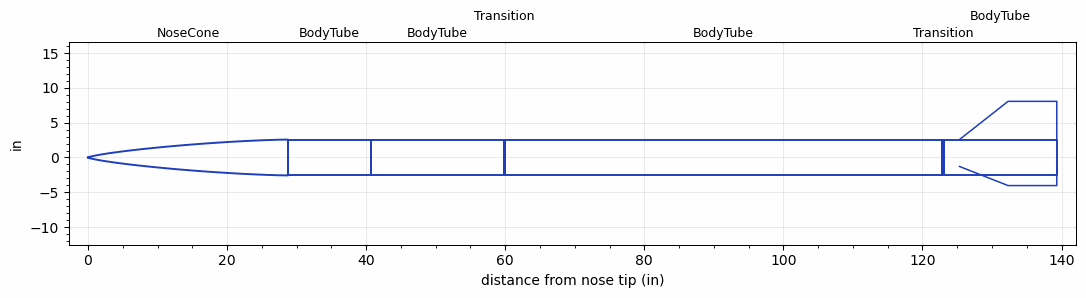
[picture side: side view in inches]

<RASAeroDocument>
 <FileVersion>2</FileVersion>
 <RocketDesign>
  <NoseCone>
   <Length>28.75</Length>
   <Diameter>5.15</Diameter>
   <Shape>Von Karman Ogive</Shape>
   <BluntRadius>0.125</BluntRadius>
   <Location>0</Location>
  </NoseCone>
  <BodyTube>
   <Length>12</Length>
   <Diameter>5.15</Diameter>
   <Location>28.75</Location>
  </BodyTube>
  <BodyTube>
   <Length>19</Length>
   <Diameter>5.15</Diameter>
   <LaunchShoeArea>0.1</LaunchShoeArea>
   <Location>40.75</Location>
  </BodyTube>
  <Transition>
   <Length>0.25</Length>
   <Diameter>5</Diameter>
   <Location>59.75</Location>
   <RearDiameter>5</RearDiameter>
  </Transition>
  <BodyTube>
   <Length>62.812</Length>
   <Diameter>5</Diameter>
   <Location>60</Location>
  </BodyTube>
  <Transition>
   <Length>0.25</Length>
   <Diameter>5.15</Diameter>
   <Location>122.812</Location>
   <RearDiameter>5.15</RearDiameter>
  </Transition>
  <BodyTube>
   <Length>16.25</Length>
   <Diameter>5.15</Diameter>
   <LaunchShoeArea>0.1</LaunchShoeArea>
   <Location>123.062</Location>
   <Fin>
    <Count>3</Count>
    <Chord>14</Chord>
    <Span>5.5</Span>
    <SweepDistance>7</SweepDistance>
    <TipChord>7</TipChord>
    <Thickness>0.125</Thickness>
    <LERadius>0.394</LERadius>
    <Location>14</Location>
    <AirfoilSection>Rounded</AirfoilSection>
    <FX1>2.1875</FX1>
    <FX3>2.1875</FX3>
   </Fin>
  </BodyTube>
  <Surface>Camouflage Paint</Surface>
  <ModifiedBarrowman>False</ModifiedBarrowman>
  <Turbulence>False</Turbulence>
  <UseBooster1>False</UseBooster1>
  <UseBooster2>False</UseBooster2>
 </RocketDesign>
 <LaunchSite>
  <Altitude>4900</Altitude>
  <Pressure>30.05</Pressure>
  <RodAngle>2</RodAngle>
  <RodLength>17</RodLength>
  <Temperature>80</Temperature>
  <WindSpeed>12.5</WindSpeed>
 </LaunchSite>
 <Recovery>
  <Altitude1>1000</Altitude1>
  <Altitude2>1000</Altitude2>
  <DeviceType1>None</DeviceType1>
  <DeviceType2>None</DeviceType2>
  <Event1>False</Event1>
  <Event2>False</Event2>
  <Size1>1</Size1>
  <Size2>1</Size2>
  <EventType1>None</EventType1>
  <EventType2>None</EventType2>
  <CD1>1.33</CD1>
  <CD2>1.33</CD2>
 </Recovery>
 <SimulationList>
  <Simulation>
   <SustainerEngine>O20300-I  (SSI)</SustainerEngine>
   <SustainerLaunchWt>71.77</SustainerLaunchWt>
   <SustainerNozzleDiameter>1.003</SustainerNozzleDiameter>
   <SustainerCG>82.68</SustainerCG>
   <SustainerIgnitionDelay>0.5</SustainerIgnitionDelay>
   <Booster1SeparationDelay>0</Booster1SeparationDelay>
   <Booster1IgnitionDelay>0</Booster1IgnitionDelay>
   <IncludeBooster1>False</IncludeBooster1>
   <Booster2Delay>0</Booster2Delay>
   <IncludeBooster2>False</IncludeBooster2>
   <TimetoApogee>44.61852</TimetoApogee>
   <MaxAltitude>28788.89</MaxAltitude>
   <MaxVelocity>1509.932</MaxVelocity>
  </Simulation>
  <Simulation>
   <SustainerEngine>N1600-T  (SSI)</SustainerEngine>
   <SustainerLaunchWt>58.6</SustainerLaunchWt>
   <SustainerNozzleDiameter>1.605</SustainerNozzleDiameter>
   <SustainerCG>76.23</SustainerCG>
   <SustainerIgnitionDelay>0.5</SustainerIgnitionDelay>
   <Booster1SeparationDelay>0</Booster1SeparationDelay>
   <Booster1IgnitionDelay>0</Booster1IgnitionDelay>
   <IncludeBooster1>False</IncludeBooster1>
   <Booster2Delay>0</Booster2Delay>
   <IncludeBooster2>False</IncludeBooster2>
   <TimetoApogee>46.05828</TimetoApogee>
   <MaxAltitude>34714.83</MaxAltitude>
   <MaxVelocity>1861.253</MaxVelocity>
  </Simulation>
  <Simulation>
   <SustainerEngine>N2000-T  (SSI)</SustainerEngine>
   <SustainerLaunchWt>58.6</SustainerLaunchWt>
   <SustainerNozzleDiameter>1.605</SustainerNozzleDiameter>
   <SustainerCG>76.23</SustainerCG>
   <SustainerIgnitionDelay>0</SustainerIgnitionDelay>
   <Booster1SeparationDelay>0</Booster1SeparationDelay>
   <Booster1IgnitionDelay>0</Booster1IgnitionDelay>
   <IncludeBooster1>False</IncludeBooster1>
   <Booster2Delay>0</Booster2Delay>
   <IncludeBooster2>False</IncludeBooster2>
   <TimetoApogee>44.18859</TimetoApogee>
   <MaxAltitude>34222.41</MaxAltitude>
   <MaxVelocity>1964.748</MaxVelocity>
  </Simulation>
  <Simulation>
   <SustainerEngine>N1100-T  (SSI)</SustainerEngine>
   <SustainerLaunchWt>58.6</SustainerLaunchWt>
   <SustainerNozzleDiameter>1.605</SustainerNozzleDiameter>
   <SustainerCG>76.23</SustainerCG>
   <SustainerIgnitionDelay>0</SustainerIgnitionDelay>
   <Booster1SeparationDelay>0</Booster1SeparationDelay>
   <Booster1IgnitionDelay>0</Booster1IgnitionDelay>
   <IncludeBooster1>False</IncludeBooster1>
   <Booster2Delay>0</Booster2Delay>
   <IncludeBooster2>False</IncludeBooster2>
   <TimetoApogee>48.93779</TimetoApogee>
   <MaxAltitude>36213.38</MaxAltitude>
   <MaxVelocity>1693.225</MaxVelocity>
  </Simulation>
  <Simulation>
   <SustainerEngine>N1850-T  (SSI)</SustainerEngine>
   <SustainerLaunchWt>58.6</SustainerLaunchWt>
   <SustainerNozzleDiameter>1.605</SustainerNozzleDiameter>
   <SustainerCG>76.23</SustainerCG>
   <SustainerIgnitionDelay>0</SustainerIgnitionDelay>
   <Booster1SeparationDelay>0</Booster1SeparationDelay>
   <Booster1IgnitionDelay>0</Booster1IgnitionDelay>
   <IncludeBooster1>False</IncludeBooster1>
   <Booster2Delay>0</Booster2Delay>
   <IncludeBooster2>False</IncludeBooster2>
   <TimetoApogee>44.67851</TimetoApogee>
   <MaxAltitude>34505.91</MaxAltitude>
   <MaxVelocity>1932.14</MaxVelocity>
  </Simulation>
  <Simulation>
   <SustainerEngine>N2250-T  (SSI)</SustainerEngine>
   <SustainerLaunchWt>58.6</SustainerLaunchWt>
   <SustainerNozzleDiameter>1.605</SustainerNozzleDiameter>
   <SustainerCG>76.23</SustainerCG>
   <SustainerIgnitionDelay>0</SustainerIgnitionDelay>
   <Booster1SeparationDelay>0</Booster1SeparationDelay>
   <Booster1IgnitionDelay>0</Booster1IgnitionDelay>
   <IncludeBooster1>False</IncludeBooster1>
   <Booster2Delay>0</Booster2Delay>
   <IncludeBooster2>False</IncludeBooster2>
   <TimetoApogee>43.24875</TimetoApogee>
   <MaxAltitude>33658.29</MaxAltitude>
   <MaxVelocity>2031.483</MaxVelocity>
  </Simulation>
 </SimulationList>
</RASAeroDocument>
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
